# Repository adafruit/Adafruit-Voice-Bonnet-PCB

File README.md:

## Adafruit Voice Bonnet PCB

<a href="http://www.adafruit.com/products/4757"><br/>
Click here to purchase one from the Adafruit shop</a>

PCB files for the Adafruit Voice Bonnet.

Format is EagleCAD schematic and board layout
* https://www.adafruit.com/product/4757

### Description

Your Raspberry Pi computer is like an electronic brain - and with the Adafruit Voice Bonnet you can give it a mouth and ears as well! Featuring two microphones and two 1 Watt speaker outputs using a high quality I2S codec, this Pi add-on will work with any Raspberry Pi with a 2x20 connector - from the Pi Zero up to the Pi 4 and beyond (basically all but the very first ones made).

The on-board WM8960 codec uses I2S digital audio for great quality recording and playback - so it sounds a lot better than the headphone jack on the Pi (or the no-headphone jack on a Pi Zero). We put ferrite beads and filter capacitors on every input and output to get the best possible performance, and all at a great price.

We specifically designed this bonnet for use with making machine learning projects such as DIY voice assistants - for example see this guide on creating a DIY Google Assistant. But you could do various voice activated or voice recognition projects. With two microphones, basic voice position can be detected as well.

* WM8960 codec uses I2S digital audio for both input and output
* On/Off privacy switch to deactivate audio so you know it can't be recording.
* Two analog microphone inputs (left and right)
* Two 1W speaker outputs
* 3.5mm stereo headphone or line-out audio
* Plugs into any Raspberry Pi with 2x20 headers

With the extra space on the PCB we also added some bonus extras!

* Push button - Use to change modes, activate the voice assistant, anything you like!
* Three DotStar RGB LEDs - add LED feedback or make a rainbow light show
* STEMMA QT connector - plug in any of our I2C sensors, OLEDs, or accessories.
* 3 Pin JST STEMMA connector - for larger accessories, like NeoPixels, a relay or servo

No assembly required! Simply pop it onto your Pi and install the microphone/speaker card using our installer script. Your Pi will then have stereo input and output for use in any software - they appear as any other speaker/mic would. Play music or record audio with ease. For audio input, the two microphones are built into the Bonnet. For audio output, you can either use the Line-out/Headphone 3.5mm stereo jack or you can plug in one or two of our enclosed speakers. For DIY speakers, solder any 1W+ speaker to one of these JST 2-PH cables. If you'd like to stack another HAT or bonnet on top, use a 2x20 stacking header to feed through the 2x20 connector.

### License

Adafruit invests time and resources providing this open source design, please support Adafruit and open-source hardware by purchasing products from [Adafruit](https://www.adafruit.com)!

Designed by Limor Fried/Ladyada for Adafruit Industries.

Creative Commons Attribution/Share-Alike, all text above must be included in any redistribution.
See license.txt for additional details.

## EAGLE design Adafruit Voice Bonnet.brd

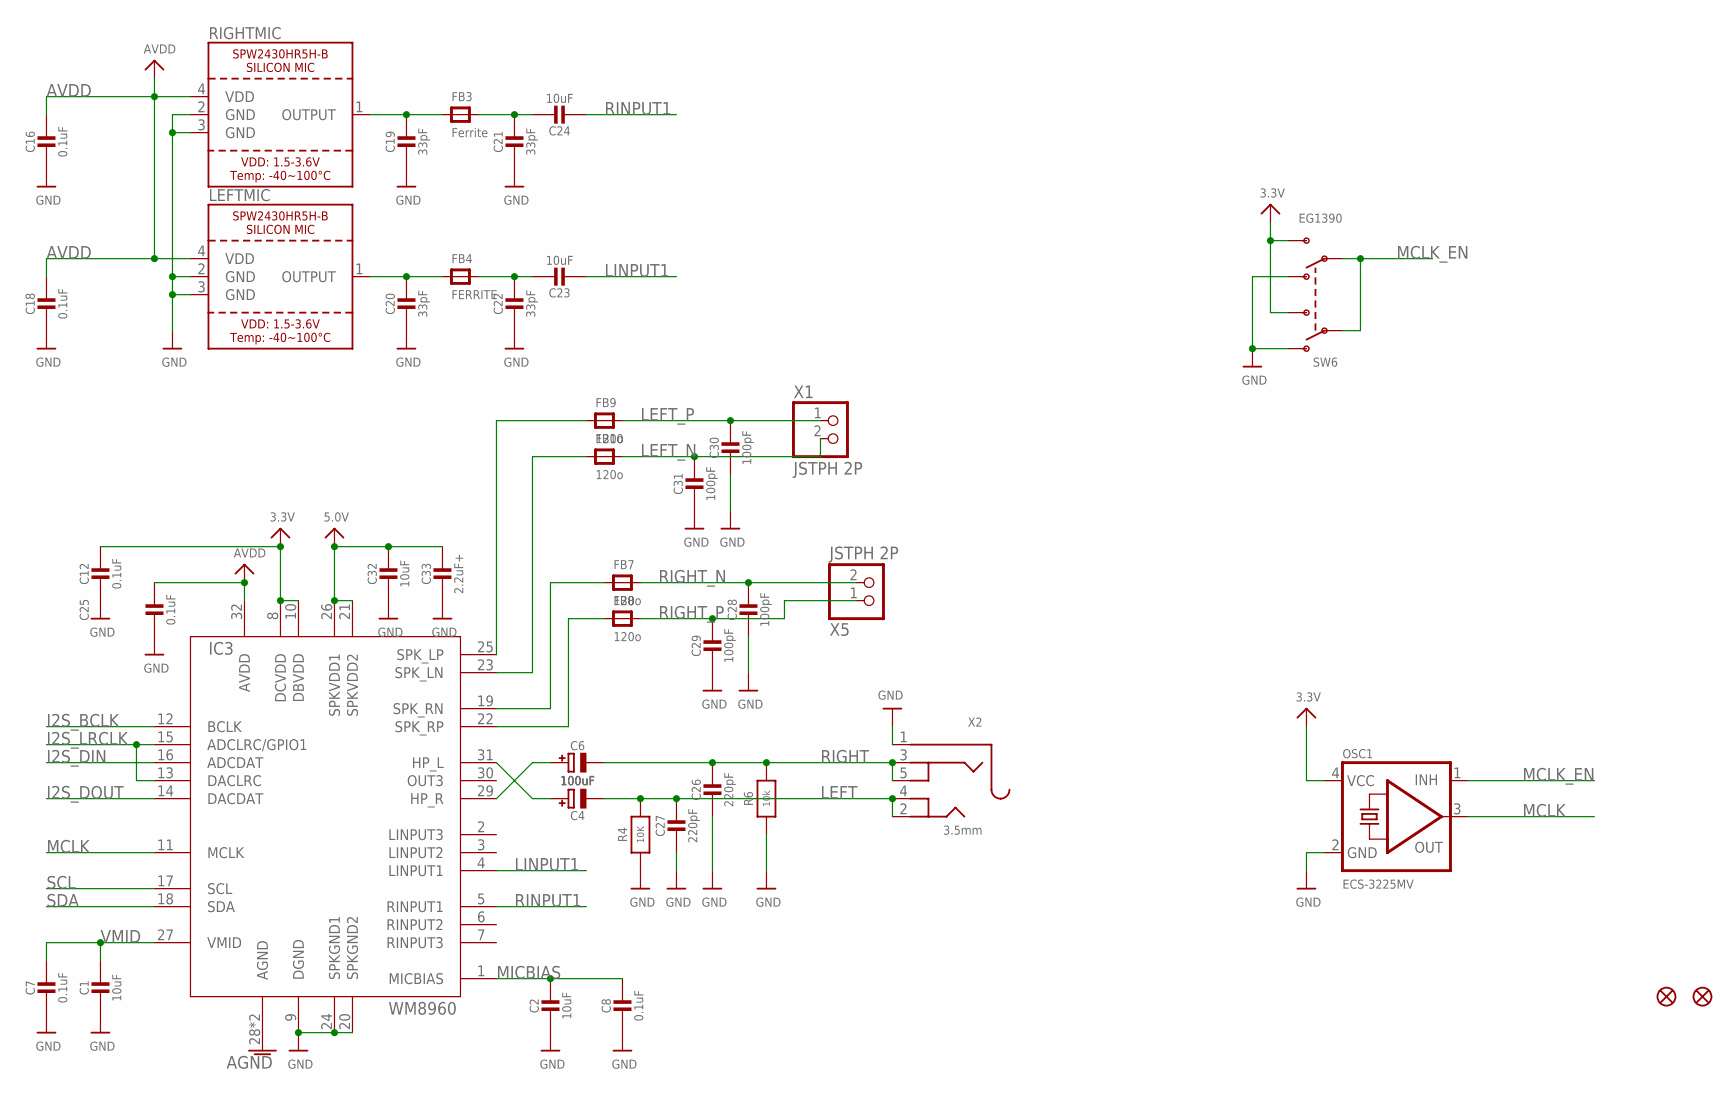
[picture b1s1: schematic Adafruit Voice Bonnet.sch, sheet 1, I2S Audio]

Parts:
C1, C2, C23, C24, C32: 10uF; 0805-NO
C4, C6: 100uF; PANASONIC_C
C7, C8, C12, C16, C18, C25: 0.1uF; 0603-NO
C19, C20, C21, C22: 33pF; 0603-NO
C26, C27: 220pF; 0603-NO
C28, C29, C30, C31: 100pF; 0603-NO
C33: 2.2uF+; 0805-NO
FB3: Ferrite; 0805-NO
FB4: FERRITE; 0805-NO
FB7, FB8, FB9, FB10: 120o; 0805-NO
FID1, FID2: FIDUCIAL_1MM
IC3: WM8960; QFN32_5MM
LEFTMIC: SPW2430HR5H-B
OSC1: ECS-3225MV; OSC_3.2X2.5MM
R4: 10K; 0603-NO
R6: 10k; 0603-NO
RIGHTMIC: SPW2430HR5H-B
SW6: EG1390
X1, X5: JSTPH 2P; JSTPH2
X2: 3.5mm; 4UCONN_19269

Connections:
3.3V: C12.1, IC3.8 (DCVDD), IC3.10 (DBVDD), OSC1.4 (VCC), SW6.S1, SW6.S2; also elsewhere on the board
5.0V: C32.1, C33.1, IC3.21 (SPKVDD2), IC3.26 (SPKVDD1); also elsewhere on the board
AGND: IC3.28 (AGND), IC3.33 (AGND); also elsewhere on the board
AVDD: C16.1, C18.1, C25.1, IC3.32 (AVDD), LEFTMIC.4 (VDD), RIGHTMIC.4 (VDD); also elsewhere on the board
GND: C1.2, C2.2, C7.2, C8.2, C12.2, C16.2, C18.2, C19.2, C20.2, C21.2, C22.2, C25.2, C26.2, C27.2, C28.2, C29.2, C30.2, C31.2, C32.2, C33.2, IC3.9 (DGND), IC3.20 (SPKGND2), IC3.24 (SPKGND1), LEFTMIC.2 (GND), LEFTMIC.3 (GND), OSC1.2 (GND), R4.1, R6.1, RIGHTMIC.2 (GND), RIGHTMIC.3 (GND), SW6.O1, SW6.O2, X2.1; also elsewhere on the board
I2S_BCLK: IC3.12 (BCLK); also elsewhere on the board
I2S_DIN: IC3.16 (ADCDAT); also elsewhere on the board
I2S_DOUT: IC3.14 (DACDAT); also elsewhere on the board
I2S_LRCLK: IC3.13 (DACLRC), IC3.15 (ADCLRC/GPIO1); also elsewhere on the board
LEFT: C4.-, C27.1, R4.2, X2.2, X2.4
LEFT_N: C31.1, FB10.2, X1.2
LEFT_P: C30.1, FB9.2, X1.1
LINPUT1: C23.2, IC3.4 (LINPUT1)
MCLK: IC3.11 (MCLK), OSC1.3 (OUT)
MCLK_EN: OSC1.1 (INH), SW6.P1, SW6.P2
MICBIAS: C2.1, C8.1, IC3.1 (MICBIAS)
unnamed: FB7.1, IC3.19 (SPK_RN)
unnamed: FB8.1, IC3.22 (SPK_RP)
unnamed: C6.+, IC3.29 (HP_R)
unnamed: C4.+, IC3.31 (HP_L)
unnamed: C19.1, FB3.1, RIGHTMIC.1 (OUTPUT)
unnamed: C20.1, FB4.1, LEFTMIC.1 (OUTPUT)
unnamed: C21.1, C24.1, FB3.2
unnamed: C22.1, C23.1, FB4.2
unnamed: FB9.1, IC3.25 (SPK_LP)
unnamed: FB10.1, IC3.23 (SPK_LN)
RIGHT: C6.-, C26.1, R6.2, X2.3, X2.5
RIGHT_N: C28.1, FB7.2, X5.2
RIGHT_P: C29.1, FB8.2, X5.1
RINPUT1: C24.2, IC3.5 (RINPUT1)
SCL: IC3.17 (SCL); also elsewhere on the board
SDA: IC3.18 (SDA); also elsewhere on the board
VMID: C1.1, C7.1, IC3.27 (VMID)

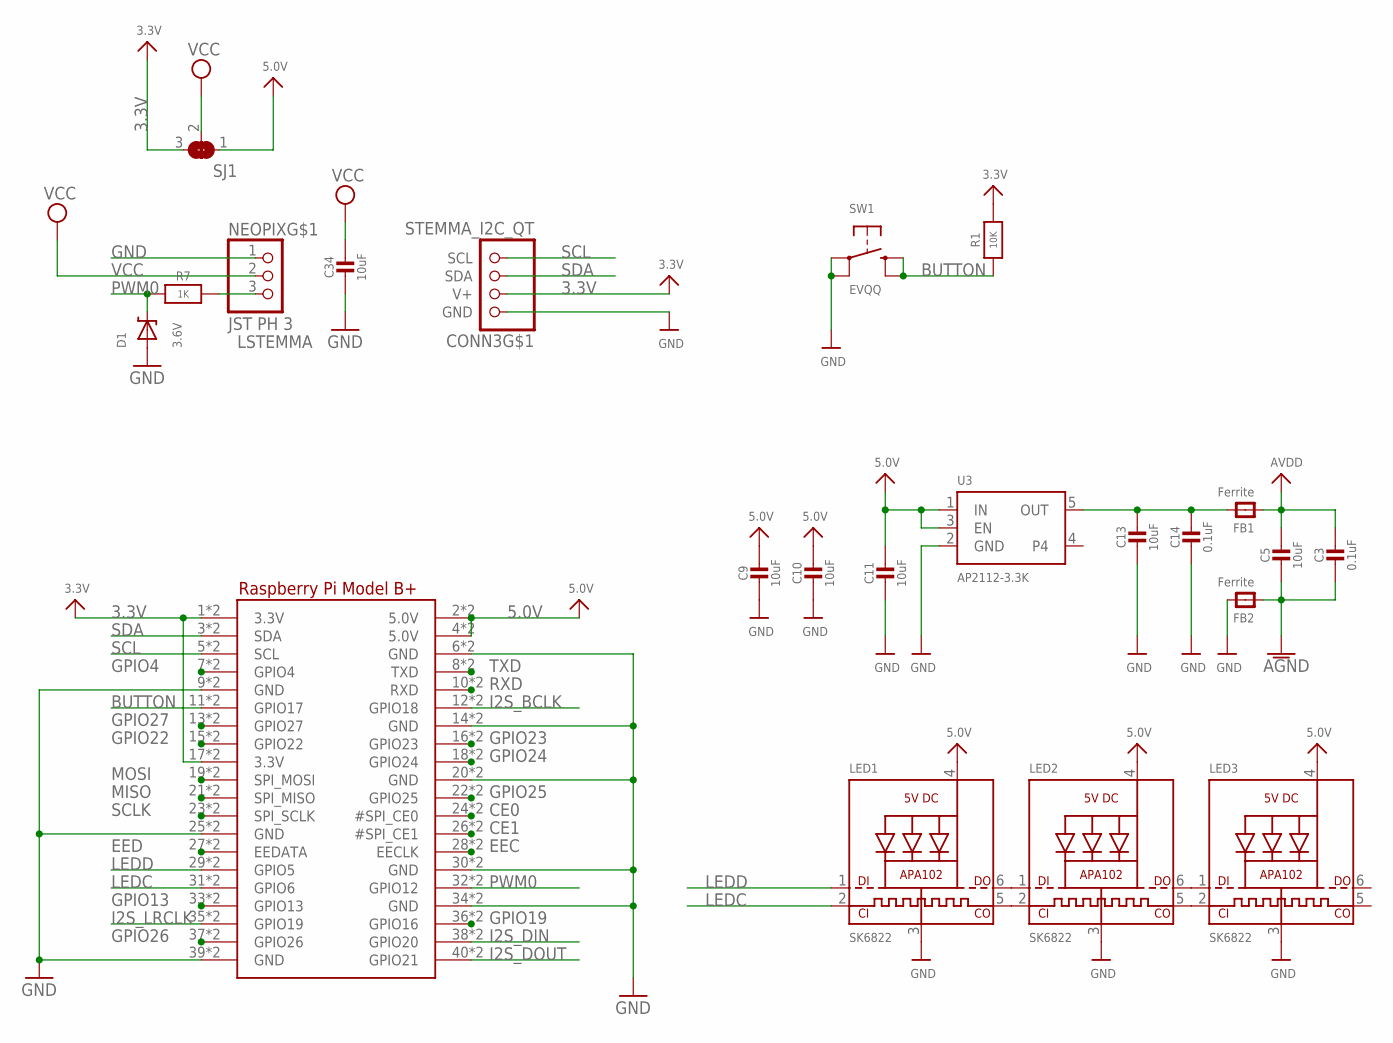
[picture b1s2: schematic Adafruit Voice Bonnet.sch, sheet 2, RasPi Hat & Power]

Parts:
C3, C14: 0.1uF; 0603-NO
C5, C9, C10, C11, C13, C34: 10uF; 0805-NO
CONN3: STEMMA_I2C_QT; JST_SH4
D1: 3.6V; SOD-323
FB1, FB2: Ferrite; 0805
LED1, LED2, LED3: SK6822; APA102
NEOPIX: JST PH 3; JSTPH3
R1: 10K; 0603-NO
R7: 1K; 0603-NO
RPI1: RASPBERRYPI_BPLUS_BONNET_THMSMT; PI_BONNET_THMSMT
SJ1: SOLDERJUMPER_2WAY; SOLDERJUMPER_2WAY_OPEN_NOPASTE
SW1: EVQQ; EVQ-Q2_SMALLER
U3: AP2112-3.3K; SOT23-5

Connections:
3.3V: CONN3.2 (V+), R1.2, RPI1.1 (3.3V), RPI1.17 (3.3V), RPI1.S1 (3.3V), RPI1.S17 (3.3V), SJ1.3; also elsewhere on the board
5.0V: C9.1, C10.1, C11.1, LED1.4 (VDD), LED2.4 (VDD), LED3.4 (VDD), RPI1.2 (5.0V), RPI1.4 (5.0V), RPI1.S2 (5.0V), RPI1.S4 (5.0V), SJ1.1, U3.1 (IN), U3.3 (EN); also elsewhere on the board
AGND: C3.2, C5.2, FB2.1; also elsewhere on the board
AVDD: C3.1, C5.1, FB1.1; also elsewhere on the board
BUTTON: R1.1, RPI1.11 (GPIO17), RPI1.S11 (GPIO17), SW1.B (S), SW1.B' (S1)
CE0: RPI1.24 (#SPI_CE0), RPI1.S24 (#SPI_CE0)
CE1: RPI1.26 (#SPI_CE1), RPI1.S26 (#SPI_CE1)
EEC: RPI1.28 (EECLK), RPI1.S28 (EECLK)
EED: RPI1.27 (EEDATA), RPI1.S27 (EEDATA)
GND: C9.2, C10.2, C11.2, C13.2, C14.2, C34.2, CONN3.1 (GND), D1.A, FB2.2, LED1.3 (GND), LED2.3 (GND), LED3.3 (GND), NEOPIX.1, RPI1.6 (GND), RPI1.9 (GND), RPI1.14 (GND), RPI1.20 (GND), RPI1.25 (GND), RPI1.30 (GND), RPI1.34 (GND), RPI1.39 (GND), RPI1.S6 (GND), RPI1.S9 (GND), RPI1.S14 (GND), RPI1.S20 (GND), RPI1.S25 (GND), RPI1.S30 (GND), RPI1.S34 (GND), RPI1.S39 (GND), SW1.A, SW1.A' (P1), U3.2 (GND); also elsewhere on the board
GPIO4: RPI1.7 (GPIO4), RPI1.S7 (GPIO4)
GPIO13: RPI1.33 (GPIO13), RPI1.S33 (GPIO13)
GPIO19: RPI1.36 (GPIO16), RPI1.S36 (GPIO16)
GPIO22: RPI1.15 (GPIO22), RPI1.S15 (GPIO22)
GPIO23: RPI1.16 (GPIO23), RPI1.S16 (GPIO23)
GPIO24: RPI1.18 (GPIO24), RPI1.S18 (GPIO24)
GPIO25: RPI1.22 (GPIO25), RPI1.S22 (GPIO25)
GPIO26: RPI1.37 (GPIO26), RPI1.S37 (GPIO26)
GPIO27: RPI1.13 (GPIO27), RPI1.S13 (GPIO27)
I2S_BCLK: RPI1.12 (GPIO18), RPI1.S12 (GPIO18); also elsewhere on the board
I2S_DIN: RPI1.38 (GPIO20), RPI1.S38 (GPIO20); also elsewhere on the board
I2S_DOUT: RPI1.40 (GPIO21), RPI1.S40 (GPIO21); also elsewhere on the board
I2S_LRCLK: RPI1.35 (GPIO19), RPI1.S35 (GPIO19); also elsewhere on the board
LEDC: LED1.2 (CKI), RPI1.31 (GPIO6), RPI1.S31 (GPIO6)
LEDD: LED1.1 (DI), RPI1.29 (GPIO5), RPI1.S29 (GPIO5)
LSTEMMA: NEOPIX.3, R7.1
MISO: RPI1.21 (SPI_MISO), RPI1.S21 (SPI_MISO)
MOSI: RPI1.19 (SPI_MOSI), RPI1.S19 (SPI_MOSI)
unnamed: LED1.6 (DO), LED2.1 (DI)
unnamed: LED1.5 (CKO), LED2.2 (CKI)
unnamed: LED2.6 (DO), LED3.1 (DI)
unnamed: LED2.5 (CKO), LED3.2 (CKI)
OUT: C13.1, C14.1, FB1.2, U3.5 (OUT)
PWM0: D1.C, R7.2, RPI1.32 (GPIO12), RPI1.S32 (GPIO12)
RXD: RPI1.10 (RXD), RPI1.S10 (RXD)
SCL: CONN3.4 (SCL), RPI1.5 (SCL), RPI1.S5 (SCL); also elsewhere on the board
SCLK: RPI1.23 (SPI_SCLK), RPI1.S23 (SPI_SCLK)
SDA: CONN3.3 (SDA), RPI1.3 (SDA), RPI1.S3 (SDA); also elsewhere on the board
TXD: RPI1.8 (TXD), RPI1.S8 (TXD)
VCC: C34.1, NEOPIX.2, SJ1.2

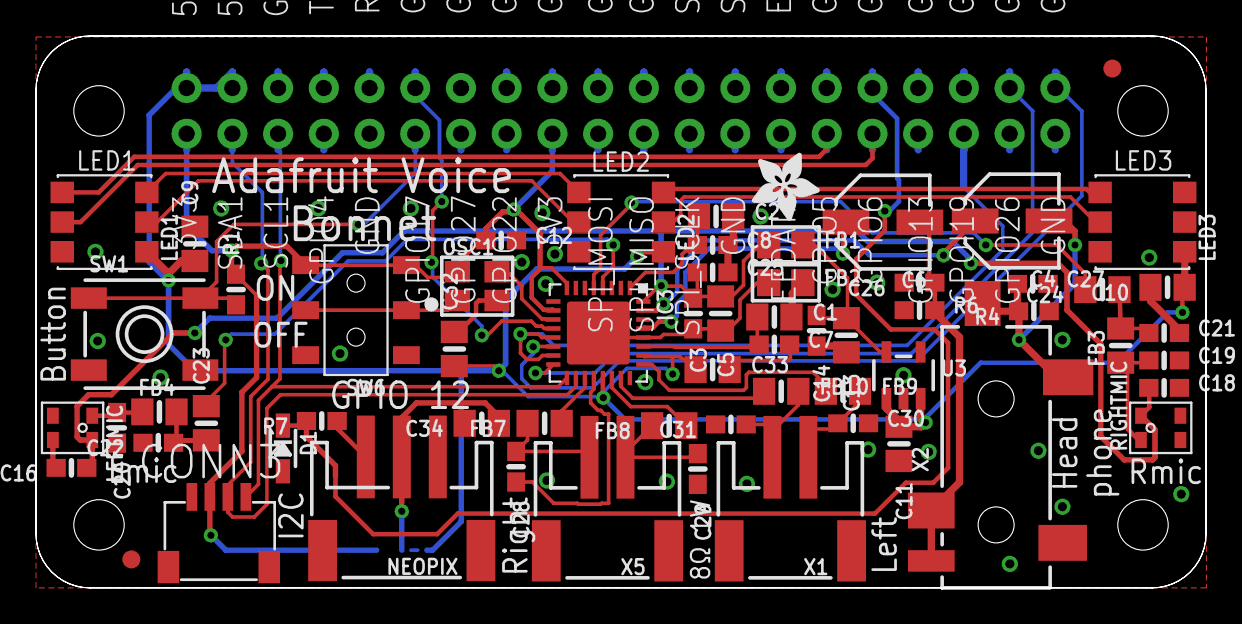
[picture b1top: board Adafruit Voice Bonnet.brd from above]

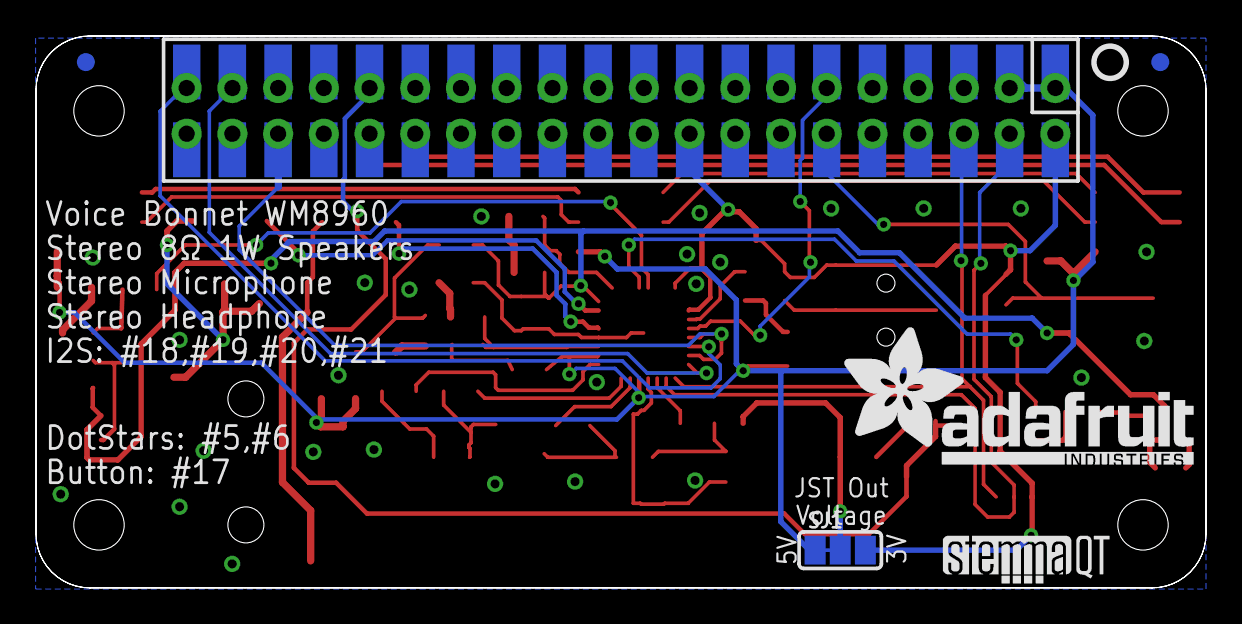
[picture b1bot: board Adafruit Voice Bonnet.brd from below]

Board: 2 copper layers, 65.0 x 30.7 mm, 69 parts (5 on the bottom side), 62 nets.

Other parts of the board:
U$11: PCBFEAT-REV-040
U$12: STEMMAQT
U$15: ADAFRUIT_3.5MM
U$16: ADAFRUIT_TEXT_20MM
U$79: BRAINPAD_1IN

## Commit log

2020-10-27 Adding board files.

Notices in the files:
parts and their libraries:
microbuilder: This work is placed in the public domain, and may be freely used for commercial and non-commercial work with the following conditions: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
